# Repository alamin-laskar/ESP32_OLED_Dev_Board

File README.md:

# ESP32_OLED_Dev_Board
# This is a learning phase design, It may not work in real life
# About
This is a custom doubled sided ESP32 dev board based on ESP32-WROOM-32D-N4, equiped with ssd1306 0.96" OLED Display and few buttons.
A I2C bus is used for the display and for the buttons five GPIO pins are used. 

Buttons Connection: 

Button      GPIO Pin

SW1   ---->  6   (Right)

SW2   ---->  7   (Down)

SW3   ---->  16  (Left)

SW4   ---->  14  (UP)

SW5   ---->  13  (OK)

For USB to UART conversion CP2102 USB to UART bridge is used.

# Exposed Pins
One SPI Bus and three GPIO pins are exposed for external device attachments

# Board Schematics
[Board Schematic.pdf](https://github.com/user-attachments/files/25577954/Board.Schematic.pdf)

# Board Images

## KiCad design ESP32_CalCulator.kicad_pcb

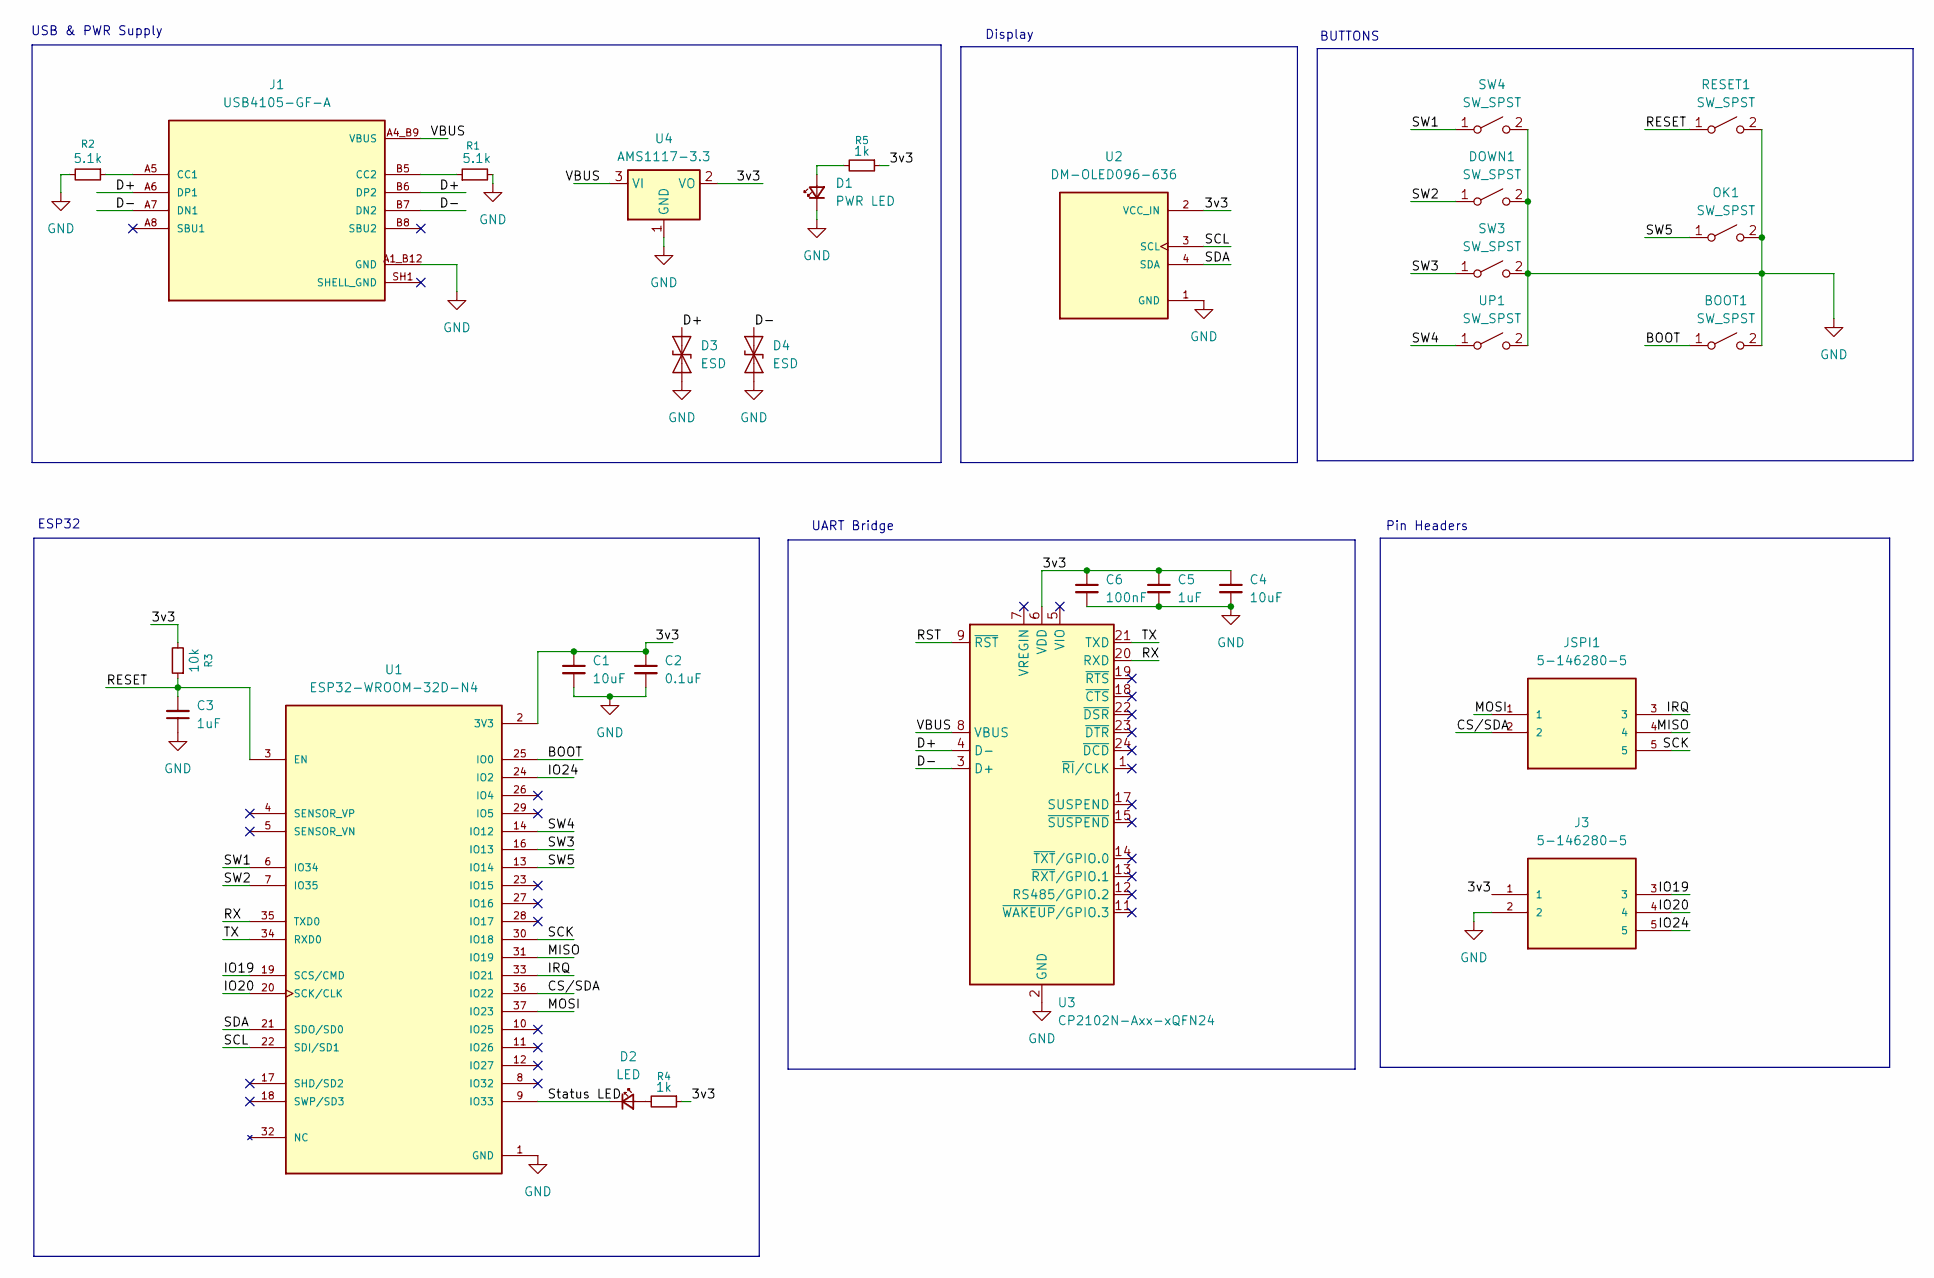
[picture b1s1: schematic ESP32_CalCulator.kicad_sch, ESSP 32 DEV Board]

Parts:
BOOT1: SW_SPST; SW_SPST_TL3342
C1, C4: 10uF; C_0402_1005Metric
C2: 0.1uF; C_0402_1005Metric
C3, C5: 1uF; C_0402_1005Metric
C6: 100nF; C_0402_1005Metric
D1: PWR LED; LED_0603_1608Metric
D2: LED; LED_0603_1608Metric
D3, D4: ESD; D_0402_1005Metric
DOWN1: SW_SPST; SW_SPST_TL3305A
J1: USB4105-GF-A; USB_C_4105-GF-A; PARTREV B4; DigiKey_Part_Number 2073-USB4105-GF-ACT-ND
J3: 5-146280-5; 5_pin_connector; PARTREV R
JSPI1: 5-146280-5; 5_pin_connector; PARTREV R
OK1: SW_SPST; SW_SPST_TL3305A
R1, R2: 5.1k; R_0402_1005Metric
R3: 10k; R_0402_1005Metric
R4, R5: 1k; R_0402_1005Metric
RESET1: SW_SPST; SW_SPST_TL3342
SW3, SW4: SW_SPST; SW_SPST_TL3305A
U1: ESP32-WROOM-32D-N4; MODULE_ESP32-WROOM-32D-N4; PARTREV 1.9; DigiKey_Part_Number 1965-ESP32-WROOM-32D-N4CT-ND
U2: DM-OLED096-636; OLED096-ssd1306; PARTREV 2018-09-10
U3: CP2102N-Axx-xQFN24; QFN-64-1EP_9x9mm_P0.5mm_EP4.1x4.1mm
U4: AMS1117-3.3; SOT-223-3_TabPin2
UP1: SW_SPST; SW_SPST_TL3305A

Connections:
/3v3: C1.1, C2.1, C4.1, C5.1, C6.1, J3.1, R3.2, R4.1, R5.1, U1.2 (3V3), U2.2 (VCC_IN), U3.6 (VDD), U4.2 (VO)
/BOOT: BOOT1.1 (A), U1.25 (IO0)
/CS/SDA: JSPI1.2, U1.36 (IO22)
/D+: D3.2 (A2), J1.A6 (DP1), J1.B6 (DP2), U3.4 (D-)
/D-: D4.1 (A1), J1.A7 (DN1), J1.B7 (DN2), U3.3 (D+)
/IO19: J3.3, U1.19 (SCS/CMD)
/IO20: J3.4, U1.20 (SCK/CLK)
/IO24: J3.5, U1.24 (IO2)
/IRQ: JSPI1.3, U1.33 (IO21)
/MISO: JSPI1.4, U1.31 (IO19)
/MOSI: JSPI1.1, U1.37 (IO23)
/RESET: C3.2, R3.1, RESET1.1 (A), U1.3 (EN)
/RST: U3.9 (~RST)
/RX: U1.35 (TXD0), U3.20 (RXD)
/SCK: JSPI1.5, U1.30 (IO18)
/SCL: U1.22 (SDI/SD1), U2.3 (SCL)
/SDA: U1.21 (SDO/SD0), U2.4 (SDA)
/SW1: SW4.1 (A), U1.6 (IO34)
/SW2: DOWN1.1 (A), U1.7 (IO35)
/SW3: SW3.1 (A), U1.16 (IO13)
/SW4: U1.14 (IO12), UP1.1 (A)
/SW5: OK1.1 (A), U1.13 (IO14)
/Status LED: D2.1 (K), U1.9 (IO33)
/TX: U1.34 (RXD0), U3.21 (TXD)
GND: BOOT1.2 (B), C1.2, C2.2, C3.1, C4.2, C5.2, C6.2, D1.1 (K), D3.1 (A1), D4.2 (A2), DOWN1.2 (B), J1.A1_B12 (GND), J1.B1_A12 (GND), J3.2, OK1.2 (B), R1.2, R2.2, RESET1.2 (B), SW3.2 (B), SW4.2 (B), U1.1 (GND), U1.15 (GND), U1.38 (GND), U1.39_1 (GND), U1.39_2 (GND), U1.39_3 (GND), U1.39_4 (GND), U1.39_5 (GND), U1.39_6 (GND), U1.39_7 (GND), U1.39_8 (GND), U1.39_9 (GND), U1.39_10 (GND), U1.39_11 (GND), U1.39_12 (GND), U1.39_13 (GND), U1.39_14 (GND), U1.39_15 (GND), U1.39_16 (GND), U1.39_17 (GND), U1.39_18 (GND), U1.39_19 (GND), U1.39_20 (GND), U1.39_21 (GND), U2.1 (GND), U3.2 (GND), U3.25 (GND), U4.1 (GND), UP1.2 (B)
unnamed: D1.2 (A), R5.2
unnamed: D2.2 (A), R4.2
unnamed: J1.A5 (CC1), R2.1
unnamed: J1.B5 (CC2), R1.1
VBUS: J1.A4_B9 (VBUS), J1.B4_A9 (VBUS), U3.8 (VBUS), U4.3 (VI)

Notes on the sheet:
UART Bridge
Display
BUTTONS
ESP32
USB & PWR Supply
Pin Headers

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
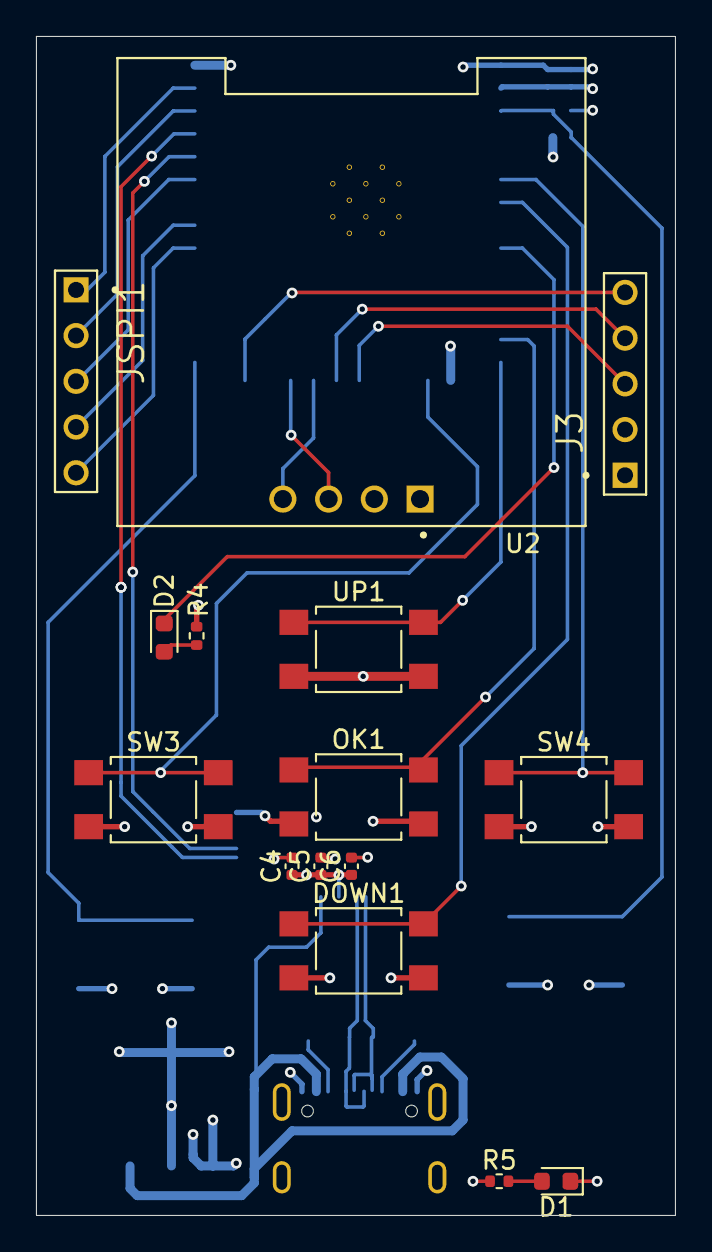
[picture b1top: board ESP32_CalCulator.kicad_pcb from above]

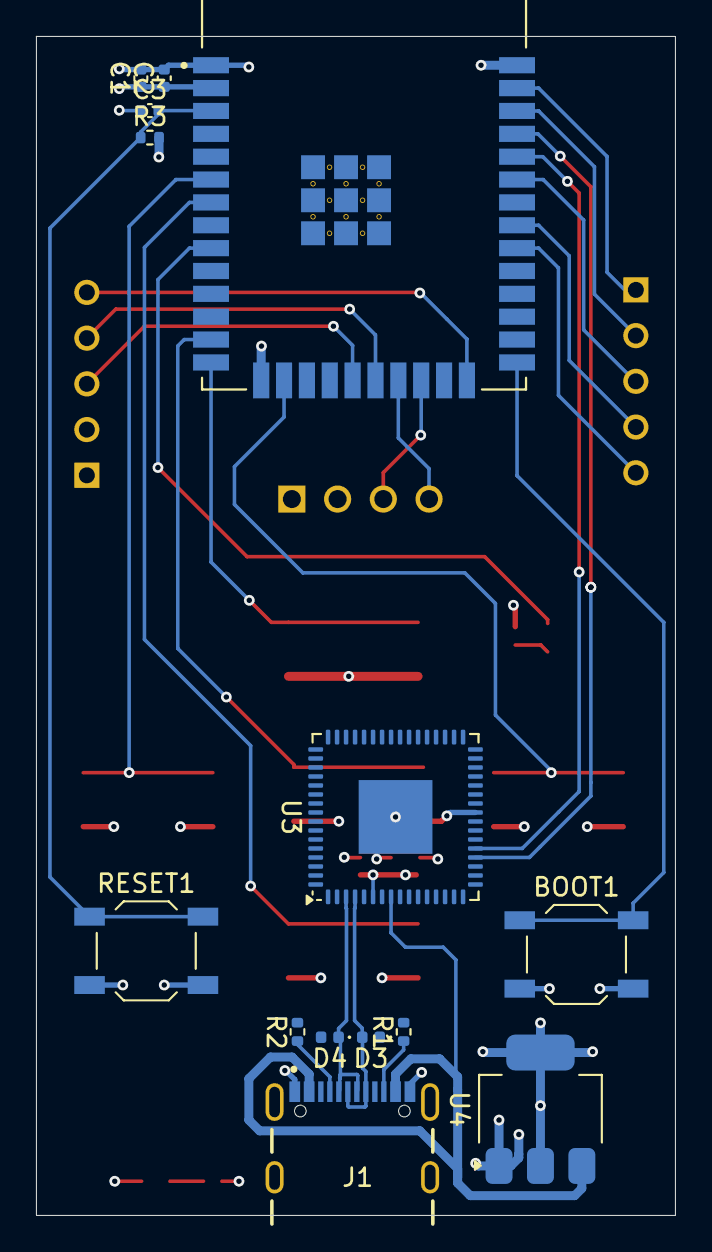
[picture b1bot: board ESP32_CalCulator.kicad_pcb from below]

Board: 4 copper layers, 35.5 x 65.5 mm, 29 parts (14 on the bottom side), 29 nets.

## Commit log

2026-02-26 added kicad files
2026-02-26 added board images and video
2026-02-26 Update README for ESP32 OLED Dev Board details
    This README provides an overview of the ESP32 OLED Dev Board, including button connections, exposed pins, board schematics, and images.
2026-02-26 Fix typo in README regarding USB to UART conversion
2026-02-26 Add new image to README.md
